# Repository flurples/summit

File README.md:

# summit
a gummy o-ring mount, mx compatible, symmetric hhkb

build video: https://youtu.be/qhuydgdiscI

## specifications
- bakeneko/unikorn style gummy o-ring mount with hhkb exclusive design
- typing angle: 7.5°
- ekh: 23.6 mm
- supported layout:

## you will need
- 1x case
- 1x weight-internal
- 1x weight-external
- 1x plate
- 1x pcb
- 1x unified daughterboard s1 (be sure to get a double sided molex cable)
- 1x gummy o-ring (I really like graveshift o-rings but any o-rings designed to work with a 60% will do)
- 6x m3 x 6mm flat head hex screws
- 4x 7.9mm diameter rubber feet (I use 3m sj5302)

## build notes
- all holes should be tapped with m3 threads.
- weight-internal and weight-external are designed to be cnc'd or laser cut from 1.6mm sheet metal, which can potentially save on manufacturing costs compared to typical 3d cnc'd weights.
- as with any gummy o-ring mount, plateless is not recommended.

## disclaimer
I do not sell any products, and I am not affiliated with any vendors who claim to sell my designs. if you choose to support these vendors, I am not responsible for any issues you may encounter with them.

## renders

## gallery
note: images are of an older version of the summit, with a different internal weight design

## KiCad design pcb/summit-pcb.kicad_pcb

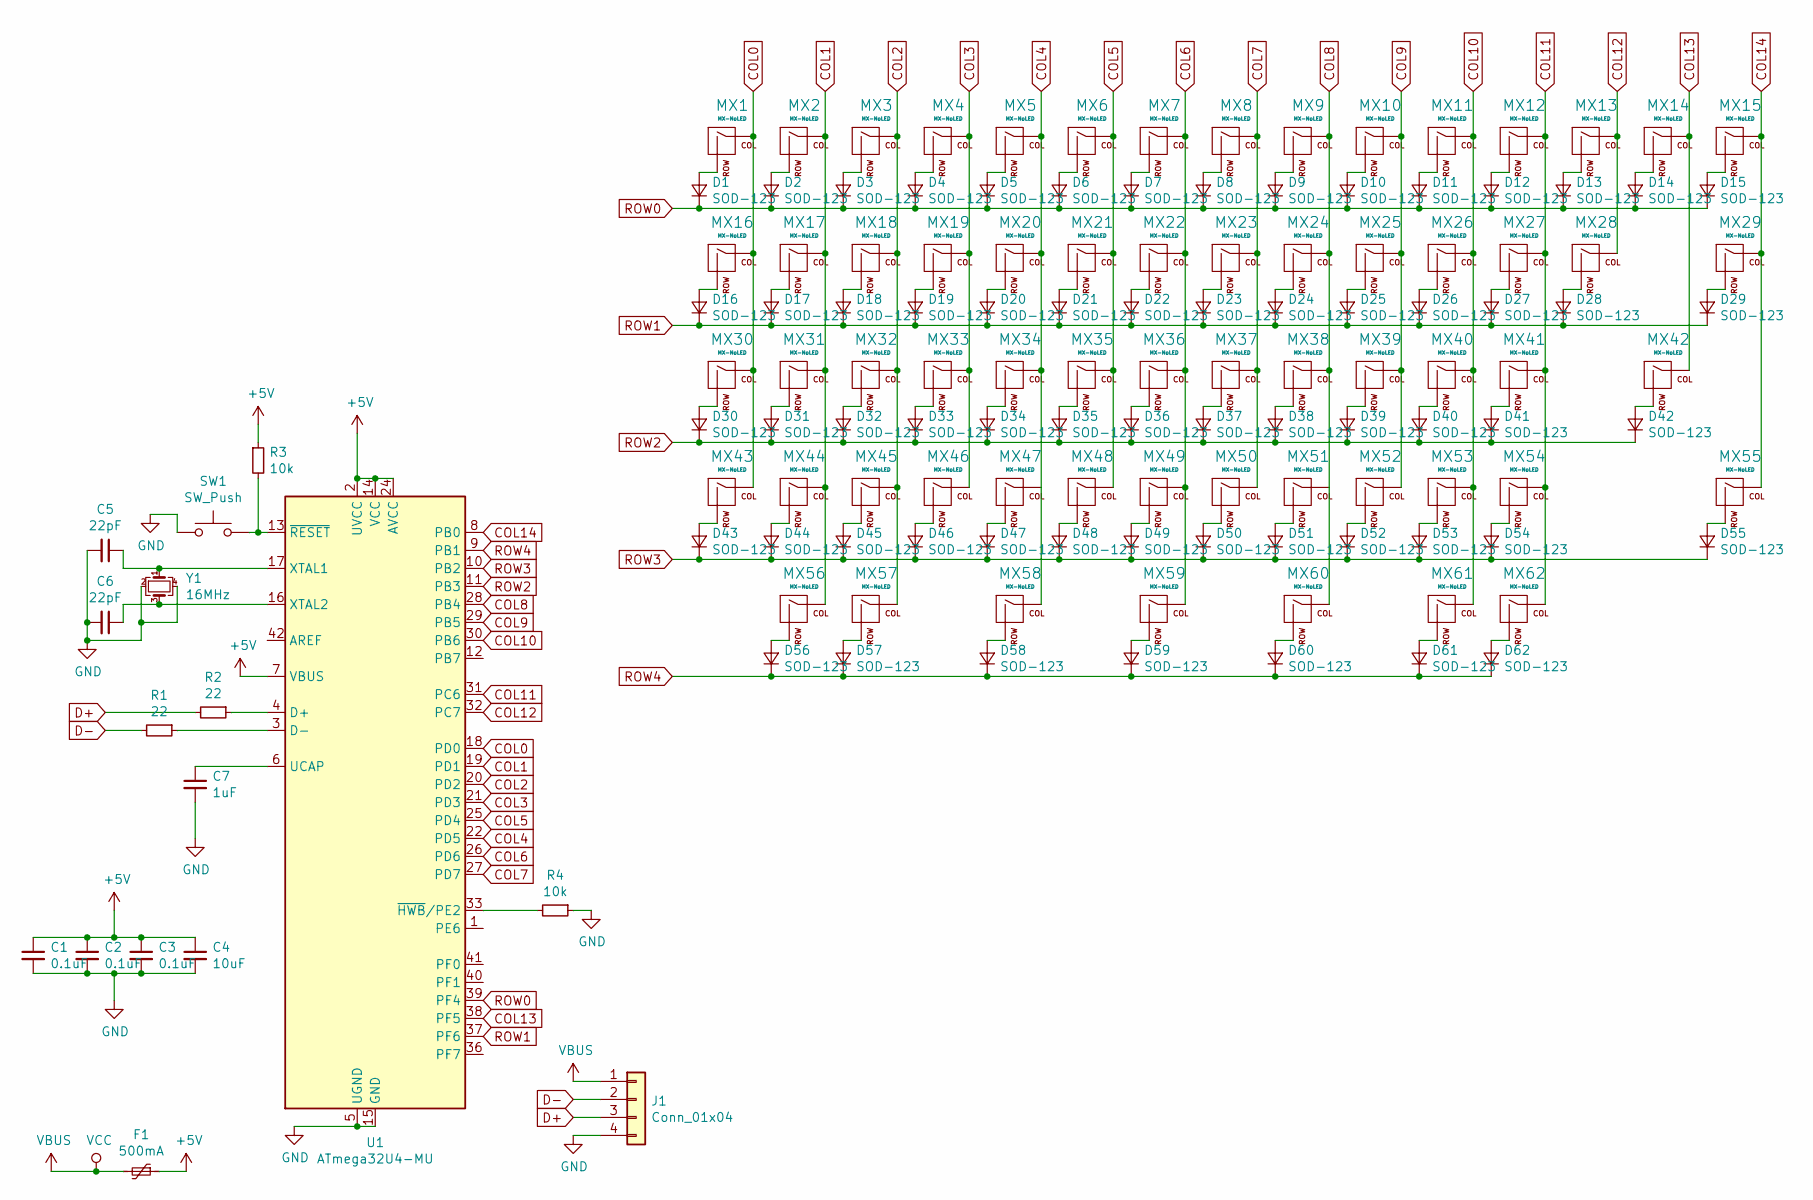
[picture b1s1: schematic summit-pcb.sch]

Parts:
C1, C2, C3: 0.1uF; C_0805_2012Metric
C4: 10uF; C_0805_2012Metric
C5, C6: 22pF; C_0805_2012Metric
C7: 1uF; C_0805_2012Metric
D1, D2, D3, D4, D5, D6, D7, D8, D9, D10, D11, D12, D13, D14, D15, D16, D17, D18, D19, D20, D21, D22, D23, D24, D25, D26, D27, D28, D29, D30, D31, D32, D33, D34, D35, D36, D37, D38, D39, D40, D41, D42, D43, D44, D45, D46, D47, D48, D49, D50, D51, D52, D53, D54, D55, D56, D57, D58, D59, D60, D61, D62: SOD-123; D_SOD-123
F1: 500mA; Fuse_1206_3216Metric
J1: Conn_01x04; Molex_Pico-EZmate_78171-0004_1x04-1MP_P1.20mm_Vertical
MX1, MX2, MX3, MX4, MX5, MX6, MX7, MX8, MX9, MX10, MX11, MX12, MX13, MX14, MX15, MX17, MX18, MX19, MX20, MX21, MX22, MX23, MX24, MX25, MX26, MX27, MX28, MX31, MX32, MX33, MX34, MX35, MX36, MX37, MX38, MX39, MX40, MX41, MX44, MX45, MX46, MX47, MX48, MX49, MX50, MX51, MX52, MX53, MX55, MX56, MX62: MX-NoLED; MXOnly-1U-NoLED
MX16, MX29, MX57, MX61: MX-NoLED; MXOnly-1.5U-NoLED
MX30, MX54: MX-NoLED; MXOnly-1.75U-NoLED
MX42: MX-NoLED; MXOnly-2.25U-NoLED
MX43: MX-NoLED; MXOnly-2.25U-ReversedStabilizers-NoLED
MX58, MX60: MX-NoLED; MXOnly-3U-ReversedStabilizers-NoLED
MX59: MX-NoLED; MX-10U-ReversedStabilizers-NoLED
R1, R2: 22; R_0805_2012Metric
R3, R4: 10k; R_0805_2012Metric
SW1: SW_Push; SKQG-1155865
U1: ATmega32U4-MU; QFN-44-1EP_7x7mm_P0.5mm_EP5.2x5.2mm
Y1: 16MHz; Crystal_SMD_3225-4Pin_3.2x2.5mm

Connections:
+5V: C1.1, C2.1, C3.1, C4.1, F1.1, R3.1, U1.2 (UVCC), U1.7 (VBUS), U1.14 (VCC), U1.24 (AVCC), U1.34 (VCC), U1.44 (AVCC)
COL0: MX1.1 (COL), MX16.1 (COL), MX30.1 (COL), MX43.1 (COL), U1.18 (PD0)
COL1: MX2.1 (COL), MX17.1 (COL), MX31.1 (COL), MX44.1 (COL), MX56.1 (COL), U1.19 (PD1)
COL2: MX3.1 (COL), MX18.1 (COL), MX32.1 (COL), MX45.1 (COL), MX57.1 (COL), U1.20 (PD2)
COL3: MX4.1 (COL), MX19.1 (COL), MX33.1 (COL), MX46.1 (COL), U1.21 (PD3)
COL4: MX5.1 (COL), MX20.1 (COL), MX34.1 (COL), MX47.1 (COL), MX58.1 (COL), U1.22 (PD5)
COL5: MX6.1 (COL), MX21.1 (COL), MX35.1 (COL), MX48.1 (COL), U1.25 (PD4)
COL6: MX7.1 (COL), MX22.1 (COL), MX36.1 (COL), MX49.1 (COL), MX59.1 (COL), U1.26 (PD6)
COL7: MX8.1 (COL), MX23.1 (COL), MX37.1 (COL), MX50.1 (COL), U1.27 (PD7)
COL8: MX9.1 (COL), MX24.1 (COL), MX38.1 (COL), MX51.1 (COL), MX60.1 (COL), U1.28 (PB4)
COL9: MX10.1 (COL), MX25.1 (COL), MX39.1 (COL), MX52.1 (COL), U1.29 (PB5)
COL10: MX11.1 (COL), MX26.1 (COL), MX40.1 (COL), MX53.1 (COL), MX61.1 (COL), U1.30 (PB6)
COL11: MX12.1 (COL), MX27.1 (COL), MX41.1 (COL), MX54.1 (COL), MX62.1 (COL), U1.31 (PC6)
COL12: MX13.1 (COL), MX28.1 (COL), U1.32 (PC7)
COL13: MX14.1 (COL), MX42.1 (COL), U1.38 (PF5)
COL14: MX15.1 (COL), MX29.1 (COL), MX55.1 (COL), U1.8 (PB0)
D+: J1.3, R2.2
D-: J1.2, R1.2
GND: C1.2, C2.2, C3.2, C4.2, C5.2, C6.2, C7.2, J1.4, R4.1, SW1.1, U1.5 (UGND), U1.15 (GND), U1.23 (GND), U1.35 (GND), U1.43 (GND), U1.45 (GND), Y1.2, Y1.4
unnamed: C5.1, U1.17 (XTAL1), Y1.1
unnamed: C6.1, U1.16 (XTAL2), Y1.3
unnamed: C7.1, U1.6 (UCAP)
unnamed: D1.2 (A), MX1.2 (ROW)
unnamed: D2.2 (A), MX2.2 (ROW)
unnamed: D3.2 (A), MX3.2 (ROW)
unnamed: D4.2 (A), MX4.2 (ROW)
unnamed: D5.2 (A), MX5.2 (ROW)
unnamed: D6.2 (A), MX6.2 (ROW)
unnamed: D7.2 (A), MX7.2 (ROW)
unnamed: D8.2 (A), MX8.2 (ROW)
unnamed: D9.2 (A), MX9.2 (ROW)
unnamed: D10.2 (A), MX10.2 (ROW)
unnamed: D11.2 (A), MX11.2 (ROW)
unnamed: D12.2 (A), MX12.2 (ROW)
unnamed: D13.2 (A), MX13.2 (ROW)
unnamed: D14.2 (A), MX14.2 (ROW)
unnamed: D15.2 (A), MX15.2 (ROW)
unnamed: D16.2 (A), MX16.2 (ROW)
unnamed: D17.2 (A), MX17.2 (ROW)
unnamed: D18.2 (A), MX18.2 (ROW)
unnamed: D19.2 (A), MX19.2 (ROW)
unnamed: D20.2 (A), MX20.2 (ROW)
unnamed: D21.2 (A), MX21.2 (ROW)
unnamed: D22.2 (A), MX22.2 (ROW)
unnamed: D23.2 (A), MX23.2 (ROW)
unnamed: D24.2 (A), MX24.2 (ROW)
unnamed: D25.2 (A), MX25.2 (ROW)
unnamed: D26.2 (A), MX26.2 (ROW)
unnamed: D27.2 (A), MX27.2 (ROW)
unnamed: D28.2 (A), MX28.2 (ROW)
unnamed: D29.2 (A), MX29.2 (ROW)
unnamed: D30.2 (A), MX30.2 (ROW)
unnamed: D31.2 (A), MX31.2 (ROW)
unnamed: D32.2 (A), MX32.2 (ROW)
unnamed: D33.2 (A), MX33.2 (ROW)
unnamed: D34.2 (A), MX34.2 (ROW)
unnamed: D35.2 (A), MX35.2 (ROW)
unnamed: D36.2 (A), MX36.2 (ROW)
unnamed: D37.2 (A), MX37.2 (ROW)
unnamed: D38.2 (A), MX38.2 (ROW)
unnamed: D39.2 (A), MX39.2 (ROW)
unnamed: D40.2 (A), MX40.2 (ROW)
unnamed: D41.2 (A), MX41.2 (ROW)
unnamed: D42.2 (A), MX42.2 (ROW)
unnamed: D43.2 (A), MX43.2 (ROW)
unnamed: D44.2 (A), MX44.2 (ROW)
unnamed: D45.2 (A), MX45.2 (ROW)
unnamed: D46.2 (A), MX46.2 (ROW)
unnamed: D47.2 (A), MX47.2 (ROW)
unnamed: D48.2 (A), MX48.2 (ROW)
unnamed: D49.2 (A), MX49.2 (ROW)
unnamed: D50.2 (A), MX50.2 (ROW)
unnamed: D51.2 (A), MX51.2 (ROW)
unnamed: D52.2 (A), MX52.2 (ROW)
unnamed: D53.2 (A), MX53.2 (ROW)
unnamed: D54.2 (A), MX54.2 (ROW)
unnamed: D55.2 (A), MX55.2 (ROW)
unnamed: D56.2 (A), MX56.2 (ROW)
unnamed: D57.2 (A), MX57.2 (ROW)
unnamed: D58.2 (A), MX58.2 (ROW)
unnamed: D59.2 (A), MX59.2 (ROW)
unnamed: D60.2 (A), MX60.2 (ROW)
unnamed: D61.2 (A), MX61.2 (ROW)
unnamed: D62.2 (A), MX62.2 (ROW)
unnamed: R1.1, U1.3 (D-)
unnamed: R2.1, U1.4 (D+)
unnamed: R3.2, SW1.2, U1.13 (~RESET)
unnamed: R4.2, U1.33 (~HWB~/PE2)
ROW0: D1.1 (K), D2.1 (K), D3.1 (K), D4.1 (K), D5.1 (K), D6.1 (K), D7.1 (K), D8.1 (K), D9.1 (K), D10.1 (K), D11.1 (K), D12.1 (K), D13.1 (K), D14.1 (K), D15.1 (K), U1.39 (PF4)
ROW1: D16.1 (K), D17.1 (K), D18.1 (K), D19.1 (K), D20.1 (K), D21.1 (K), D22.1 (K), D23.1 (K), D24.1 (K), D25.1 (K), D26.1 (K), D27.1 (K), D28.1 (K), D29.1 (K), U1.37 (PF6)
ROW2: D30.1 (K), D31.1 (K), D32.1 (K), D33.1 (K), D34.1 (K), D35.1 (K), D36.1 (K), D37.1 (K), D38.1 (K), D39.1 (K), D40.1 (K), D41.1 (K), D42.1 (K), U1.11 (PB3)
ROW3: D43.1 (K), D44.1 (K), D45.1 (K), D46.1 (K), D47.1 (K), D48.1 (K), D49.1 (K), D50.1 (K), D51.1 (K), D52.1 (K), D53.1 (K), D54.1 (K), D55.1 (K), U1.10 (PB2)
ROW4: D56.1 (K), D57.1 (K), D58.1 (K), D59.1 (K), D60.1 (K), D61.1 (K), D62.1 (K), U1.9 (PB1)
VBUS: F1.2, J1.1

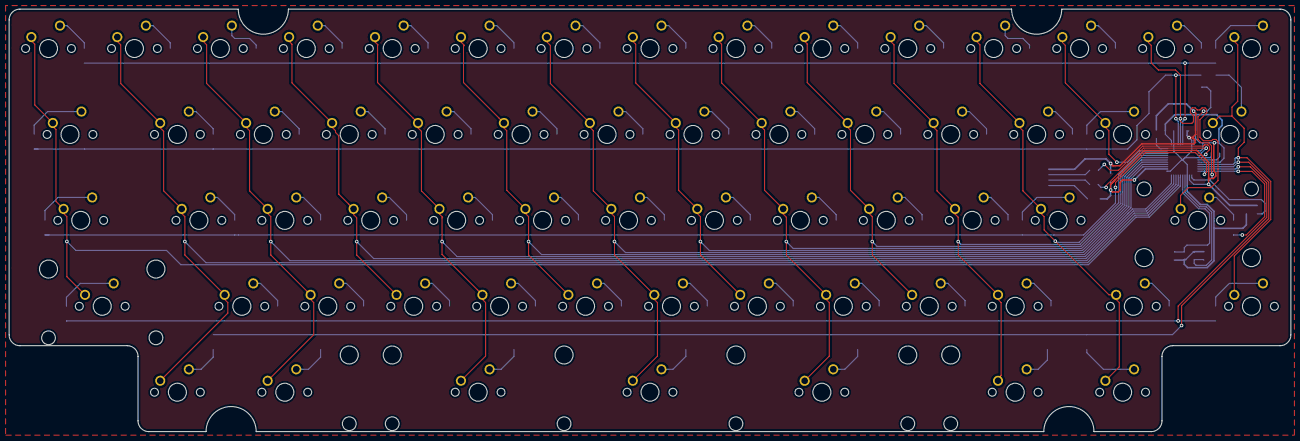
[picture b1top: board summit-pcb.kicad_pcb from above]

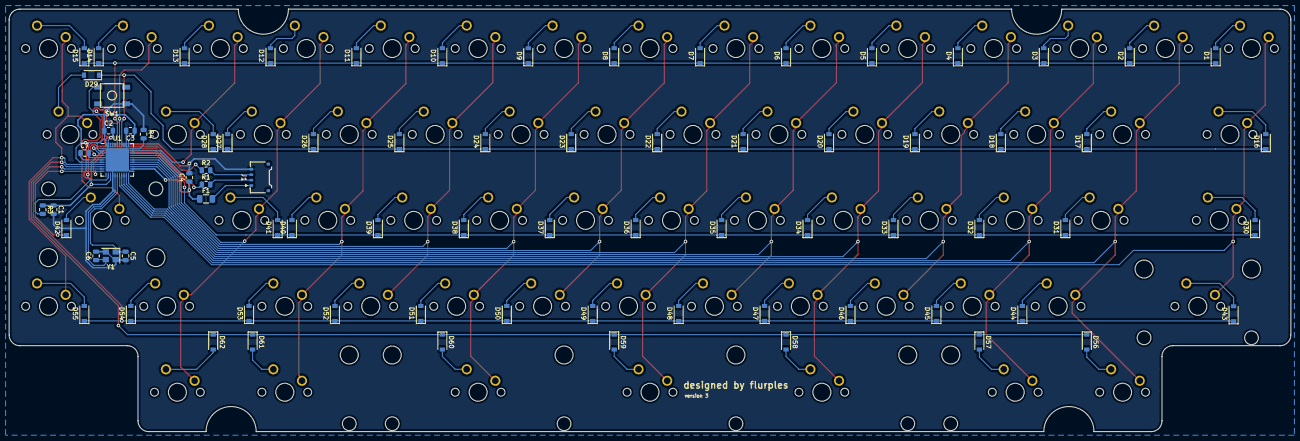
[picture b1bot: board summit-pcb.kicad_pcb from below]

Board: 2 copper layers, 284.2 x 93.7 mm, 140 parts (78 on the bottom side), 94 nets.

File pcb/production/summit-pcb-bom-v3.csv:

Comment,Designator,Footprint,LCSC Part Number
0.1uF,"C1,C2,C3",Capacitor_SMD:C_0805_2012Metric,C1711
10uF,C4,Capacitor_SMD:C_0805_2012Metric,C17024
22pF,"C5,C6",Capacitor_SMD:C_0805_2012Metric,C1804
1uF,C7,Capacitor_SMD:C_0805_2012Metric,C28323
SOD-123,"D1,D2,D3,D4,D5,D6,D7,D8,D9,D10,D11,D12,D13,D14,D15,D16,D17,D18,D19,D20,D21,D22,D23,D24,D25,D26,D27,D28,D29,D30,D31,D32,D33,D34,D35,D36,D37,D38,D39,D40,D41,D42,D43,D44,D45,D46,D47,D48,D49,D50,D51,D52,D53,D54,D55,D56,D57,D58,D59,D60,D61,D62",Diode_SMD:D_SOD-123,C2099
500mA,F1,Fuse:Fuse_1206_3216Metric,C369160
Conn_01x04,J1,Connector_Molex:Molex_Pico-EZmate_78171-0004_1x04-1MP_P1.20mm_Vertical,C2829871
22,"R1,R2",Resistor_SMD:R_0805_2012Metric,C17561 
10k,"R3,R4",Resistor_SMD:R_0805_2012Metric,C17414
SW_Push,SW1,random-keyboard-parts:SKQG-1155865,C5140332
ATmega32U4-MU,U1,Package_DFN_QFN:QFN-44-1EP_7x7mm_P0.5mm_EP5.2x5.2mm,C112161
16MHz,Y1,Crystal:Crystal_SMD_3225-4Pin_3.2x2.5mm,C13738
